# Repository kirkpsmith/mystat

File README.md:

# mystat

A USB-controlled potentiostat/galvanostat for electrochemistry measurements.

## Introduction
This repository contains all the necessary design files to build a USB-controlled potentiostat/galvanostat.  This repository is a modification of the original [tdstatv3](https://github.com/thomasdob/tdstatv3) designed by Thomas Dobbelaere and described in detail at https://arxiv.org/pdf/1701.07650.pdf.  The purpose of this fork is to make design changes that facilitate placing the instrument inside a protected enclosure suitable for an electrochemical research environment, including a wet chemical lab bench, fume hood, or glove box.

This version of the hardware design uses a PCB with dimensions of 55.5 mm by 70 mm to fit an EMI-shielded [extruded aluminum case](https://www.hammfg.com/files/parts/pdf/1457C801E.pdf) (IP 54 rated).  This board will also fit a similar watertight [extruded aluminum case](https://www.hammfg.com/files/parts/pdf/1457C801.pdf) (IP 65 rated).  The terminal block and surface mounted USB mini-B connector in the original tdstav3 design by Thomas Dobbelaere were replaced with IP 67 rated circular connectors for the USB and electrode cables.

In order to fit the case, tall components (such as the reed relays and crystal) had to be moved from the board edges that slide into the slots in the extruded aluminum.  As a result, the entire PCB layout was changed.  All traces were made as wide as possible given the PCB size constraints and component footprints.  In addition, this forked design eliminates the power and mode LEDs present in the original tdstatv3.  The choice to eliminate LEDs was made to avoid the need for creating holes in the case that would accommodate them.

## USB access on Linux
In order to access the device without requiring root privileges, create a file
`/etc/udev/rules.d/99-tdstatv3.rules` containing the line

```
SUBSYSTEM=="usb", ATTRS{idVendor}=="a0a0", ATTRS{idProduct}=="0002", GROUP="plugdev", MODE="0666"
```

If you are using an Arduino or similar to control pumps for flow battery experiments, you will need to make a similar file for that device, for example
`/etc/udev/rules.d/99-arduino.rules` and
```
SUBSYSTEM=="usb", ATTR{idVendor}=="1a86", ATTR{idProduct}=="7523", GROUP="plugdev", MODE="0666"
```

This assumes that the current user is a member of the `plugdev` group, and that the default USB Vendor and Product ID's
as coded in the microcontroller firmware are used; if not, these values need to be adjusted.

Reload of rules may be needed:
```
sudo udevadm control --reload
sudo udevadm trigger
```

## Windows Driver

To install the USB drivers in Windows, you must have Windows version 7 or later.  Download and run the program Zadig.exe found [here](https://github.com/pbatard/libwdi/releases/download/v1.5.1/zadig-2.9.exe).  The potentiostat should appear in the device list as "USB potentiostat/galvanostat".  Install the driver named "libusbK".

More information on Zadig can be found from its authors at: https://zadig.akeo.ie/

Zadig is based on libwdi and is licensed under GPLv3. The Zadig source code is found in the examples directory of the libwdi archive. The latest version of the source code may be downloaded from the git repository: https://github.com/pbatard/libwdi

## Credits
tdstatv3 created by:

* Thomas Dobbelaere
* email: thomas.dobbelaere@gmail.com

Previous fork created by:

* Matthew Yates
* email: myates@che.rochester.edu

Current fork created by:

* [Daniel Fernandez Pinto](https://chemisting.com) and [Kirk Smith](https://dualpower.supply)

## License
The contents of this repository are licensed under the GNU General Public License (GPL).

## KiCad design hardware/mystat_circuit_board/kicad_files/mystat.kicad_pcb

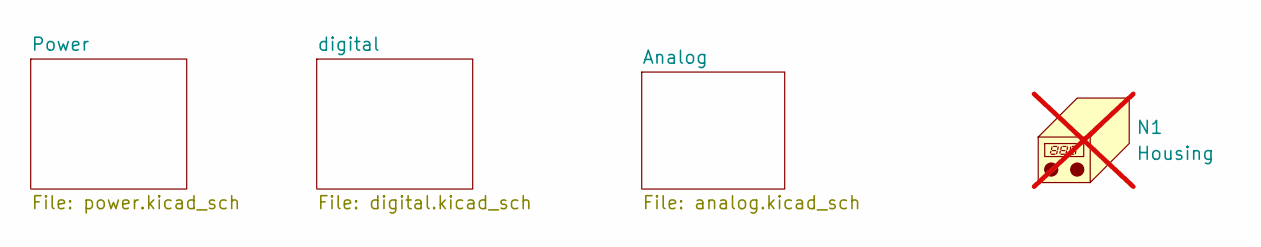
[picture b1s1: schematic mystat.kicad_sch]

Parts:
N1: Housing; MPN 1455B802; not fitted

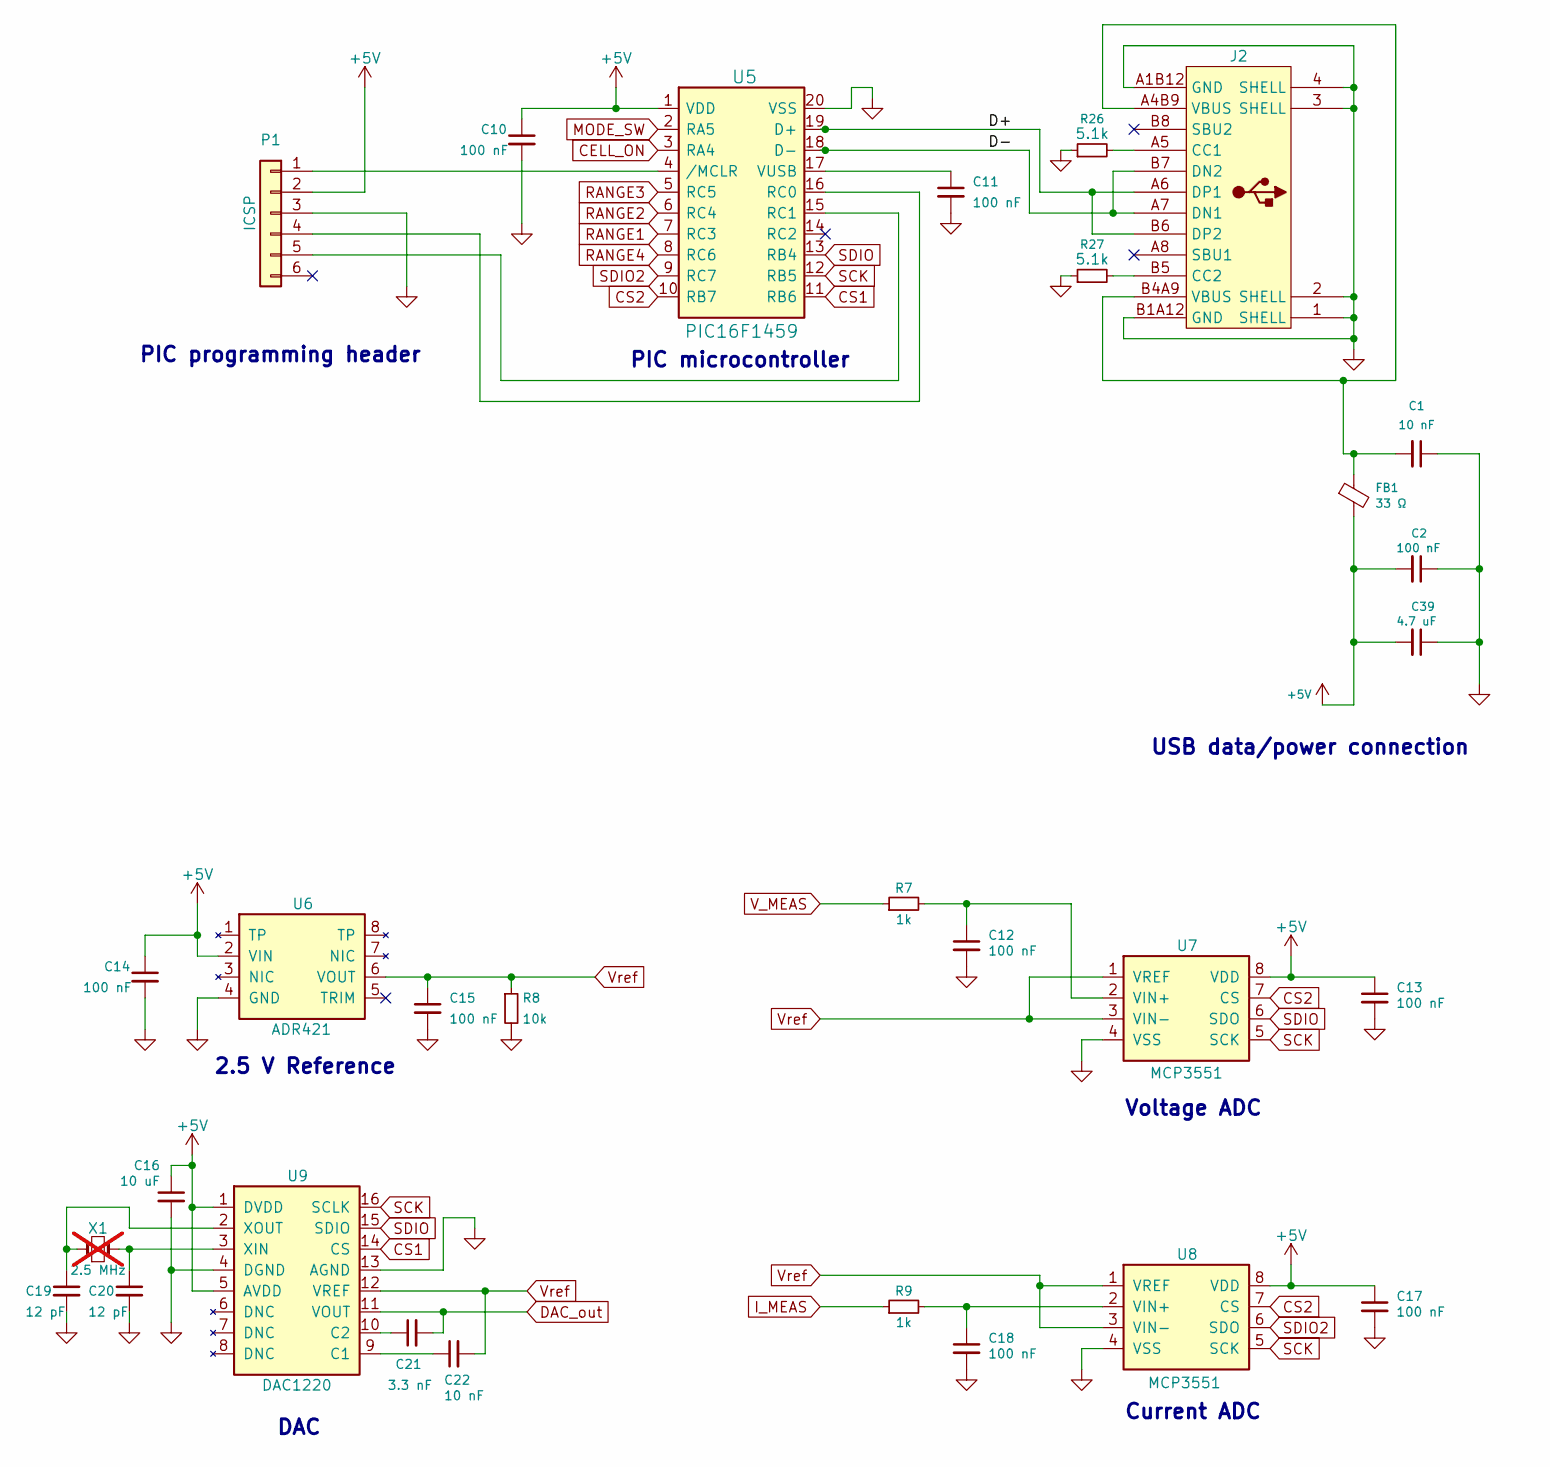
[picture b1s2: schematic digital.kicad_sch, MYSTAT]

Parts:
C1, C22: 10 nF; C_0805_2012Metric; MPN C0805C103J5GACTU
C2, C10, C11, C12, C13, C14, C15, C17, C18: 100 nF; C_0805_2012Metric; MPN 08055C104KAT2A
C16: 10 uF; C_1210_3225Metric; MPN CL32B106KBJNNWE
C19, C20: 12 pF; C_0805_2012Metric; MPN CC0805JRNPO9BN120
C21: 3.3 nF; C_0805_2012Metric; MPN GRM2165C1H332JA01D
C39: 4.7 uF; C_0805_2012Metric; MPN C2012X7R1V475K125AC
FB1: 33 Ω; C_0805_2012Metric; MPN APBH2012-330WTD16; LCSC Part C50326194
J2: USB_C_Receptacle_G-Switch_GT-USB-7010ASV; MPN GT-USB-7010ASV; LCSC Part C2988369
P1: ICSP; PinHeader_1x06_P2.54mm_Vertical; MPN HX PZ2.54-1x6P ZZ; LCSC Part C32713272
R7, R9: 1k; R_0805_2012Metric; MPN RC0805FR-071KL
R8: 10k; R_0805_2012Metric; MPN RC0805FR-0710KL
R26, R27: 5.1k; R_0805_2012Metric; LCSC Part C27834
U5: PIC16F1459; SOIC-20W; MPN PIC16F1459-I/SO
U6: ADR421; SOIC-8; MPN ADR421ARZ
U7, U8: MCP3551; SOIC-8; MPN MCP3551-E/SN; LCSC Part C1520170
U9: DAC1220; MPN DAC1220E
X1: 2.5 MHz; Crystal_HC49-U_Vertical; MPN ECS-25-S-1X; not fitted

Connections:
+5V: C2.2, C10.1, C13.1, C14.1, C16.1, C17.1, C39.2, FB1.2, P1.2, U5.1 (VDD), U6.2 (VIN), U7.8 (VDD), U8.8 (VDD), U9.1 (DVDD), U9.5 (AVDD)
/digital/D+: J2.A6 (DP1), J2.B6 (DP2), U5.19 (D+)
/digital/D-: J2.A7 (DN1), J2.B7 (DN2), U5.18 (D-)
CELL_ON: U5.3 (RA4); also elsewhere on the board
CS1: U5.11 (RB6), U9.14 (CS)
CS2: U5.10 (RB7), U7.7 (CS), U8.7 (CS)
DAC_out: C21.2, U9.11 (VOUT); also elsewhere on the board
GND: C1.1, C2.1, C10.2, C11.2, C12.2, C13.2, C14.2, C15.2, C16.2, C17.2, C18.2, C19.2, C20.2, C39.1, J2.1 (SHELL), J2.2 (SHELL), J2.3 (SHELL), J2.4 (SHELL), J2.A1B12 (GND), J2.B1A12 (GND), P1.3, R8.2, R26.1, R27.1, U5.20 (VSS), U6.4 (GND), U7.4 (VSS), U8.4 (VSS), U9.4 (DGND), U9.13 (AGND); also elsewhere on the board
I_MEAS: R9.1; also elsewhere on the board
MODE_SW: U5.2 (RA5); also elsewhere on the board
unnamed: C1.2, FB1.1, J2.A4B9 (VBUS), J2.B4A9 (VBUS)
unnamed: J2.A5 (CC1), R26.2
unnamed: J2.B5 (CC2), R27.2
unnamed: P1.1, U5.4 (/MCLR)
unnamed: P1.4, U5.16 (RC0)
unnamed: P1.5, U5.15 (RC1)
unnamed: C11.1, U5.17 (VUSB)
unnamed: C12.1, R7.2, U7.2 (VIN+)
unnamed: C18.1, R9.2, U8.2 (VIN+)
unnamed: C22.1, U9.9 (C1)
unnamed: C21.1, U9.10 (C2)
unnamed: C20.1, U9.3 (XIN), X1.2
unnamed: C19.1, U9.2 (XOUT), X1.1
RANGE1: U5.7 (RC3); also elsewhere on the board
RANGE2: U5.6 (RC4); also elsewhere on the board
RANGE3: U5.5 (RC5); also elsewhere on the board
RANGE4: U5.8 (RC6); also elsewhere on the board
SCK: U5.12 (RB5), U7.5 (SCK), U8.5 (SCK), U9.16 (SCLK)
SDIO: U5.13 (RB4), U7.6 (SDO), U9.15 (SDIO)
SDIO2: U5.9 (RC7), U8.6 (SDO)
V_MEAS: R7.1; also elsewhere on the board
Vref: C15.1, C22.2, R8.1, U6.6 (VOUT), U7.1 (VREF), U7.3 (VIN-), U8.1 (VREF), U8.3 (VIN-), U9.12 (VREF); also elsewhere on the board

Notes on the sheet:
Voltage ADC
Current ADC
PIC microcontroller
2.5 V Reference
USB data/power connection
PIC programming header
DAC

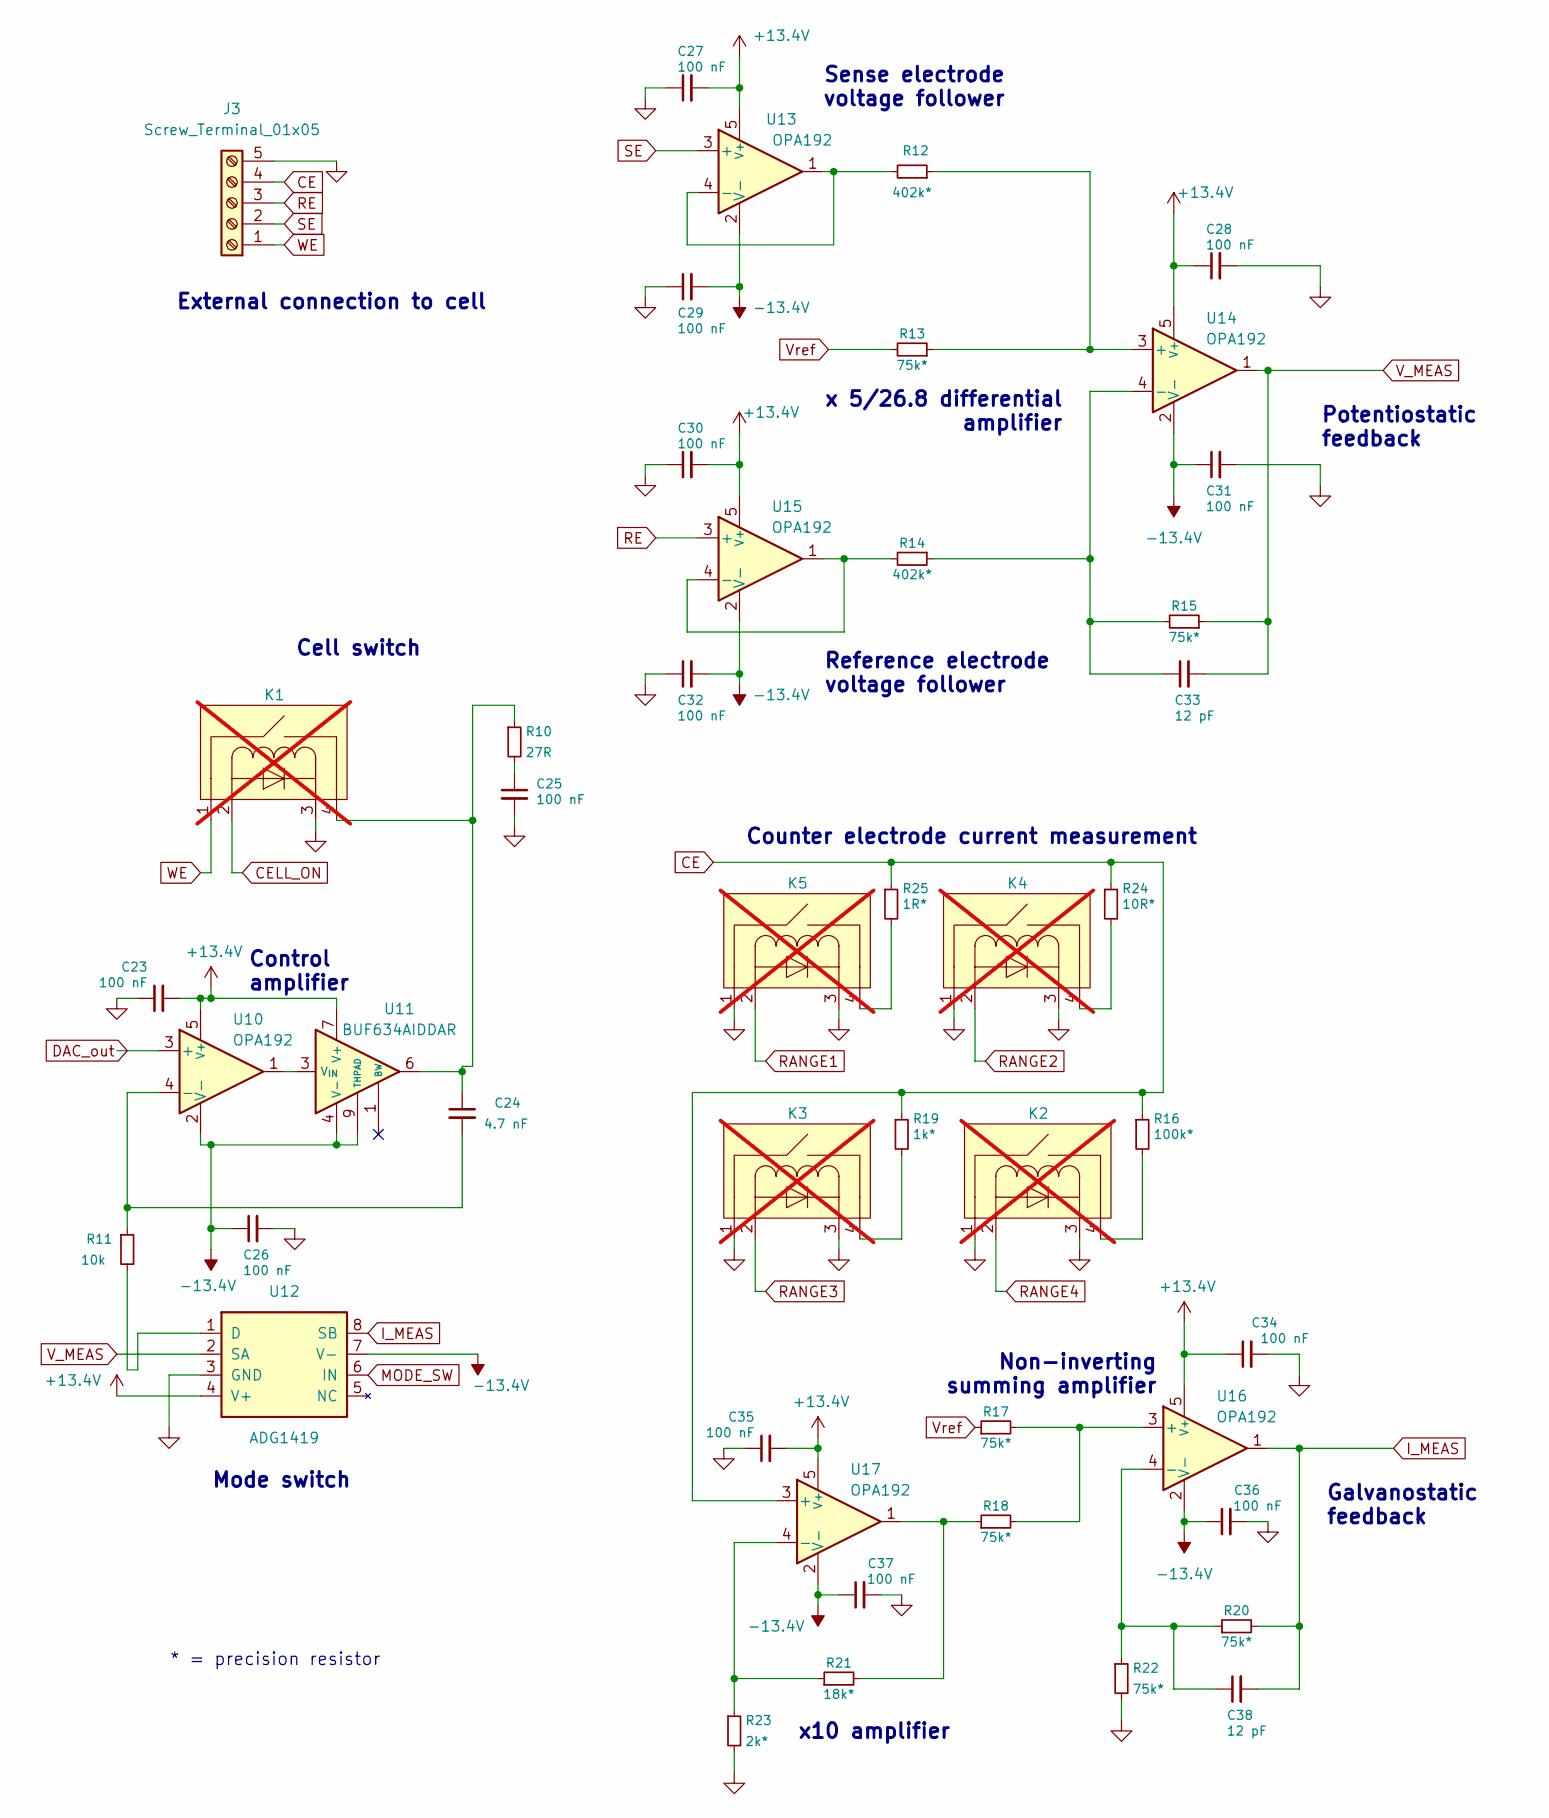
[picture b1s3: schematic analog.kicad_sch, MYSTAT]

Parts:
C23, C25, C26, C27, C28, C29, C30, C31, C32, C34, C35, C36, C37: 100 nF; C_0805_2012Metric; MPN CC0805KRX7R9BB104; LCSC Part C49678
C24: 4.7 nF; C_0805_2012Metric; MPN CC0805KRX7R9BB472; LCSC Part C107153
C33, C38: 12 pF; C_0603_1608Metric; MPN CL10C120JB8NNNC; LCSC Part C38523
J3: Screw_Terminal_01x05; CONN-TH_5P-P2.54_MX128-2.54-05P-GN01-CU-Y-A; MPN MX128-2.54-05P-GN01-Cu-Y-A; LCSC Part C5188445
K1, K2, K3, K4, K5: SIP-4_L19.6-W5.4-P5.08_9007-SPST-NO; MPN 9007-05-01; LCSC Part C6111158; not fitted
R10: 27R; R_0805_2012Metric; MPN 0805W8F270JT5E; LCSC Part C17594
R11: 10k; R_0805_2012Metric; MPN RC0805FR-0710KL; LCSC Part C84376
R12, R14: 402k*; R_0805_2012Metric; MPN TC0525B4023T5E; LCSC Part C425384
R13, R15, R17, R18, R20, R22: 75k*; R_0805_2012Metric; MPN ERA-6AEB753V; LCSC Part C473313
R16: 100k*; R_0805_2012Metric; MPN ERA-6AEB104V; LCSC Part C192074
R19: 1k*; R_0805_2012Metric; MPN ERA-6AEB102V; LCSC Part C192073
R21: 18k*; R_0805_2012Metric; MPN ERA-6AEB183V; LCSC Part C473303
R23: 2k*; R_0805_2012Metric; MPN ERA-6AEB202V; LCSC Part C417117
R24: 10R*; R_1206_3216Metric; MPN RT1206BRD0710RL; LCSC Part C309661
R25: 1R*; R_1206_3216Metric; MPN RT1206BRD071RL; LCSC Part C513714
U10, U13, U14, U15, U16, U17: OPA192; MPN OPA192IDBVR; LCSC Part C139648
U11: BUF634AIDDAR; TI_SO-PowerPAD-8_ThermalVias; MPN BUF634AIDDAR; LCSC Part C2864582
U12: ADG1419; MSOP-8_3x3mm_P0.65mm; MPN ADG1419BRMZ; LCSC Part C459694

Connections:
+13.4V: C23.2, C27.2, C28.1, C30.2, C34.1, C35.2, U10.5 (V+), U11.7 (V+), U12.4 (V+), U13.5 (V+), U14.5 (V+), U15.5 (V+), U16.5 (V+), U17.5 (V+); also elsewhere on the board
-13.4V: C26.1, C29.2, C31.1, C32.2, C36.1, C37.1, U10.2 (V-), U11.4 (V-), U11.9 (THPAD), U12.7 (V-), U13.2 (V-), U14.2 (V-), U15.2 (V-), U16.2 (V-), U17.2 (V-); also elsewhere on the board
CE: J3.4, R16.1, R19.1, R24.1, R25.1, U17.3 (+)
CELL_ON: K1.2; also elsewhere on the board
DAC_out: U10.3 (+); also elsewhere on the board
GND: C23.1, C25.2, C26.2, C27.1, C28.2, C29.1, C30.1, C31.2, C32.1, C34.2, C35.1, C36.2, C37.2, J3.5, K1.3, K2.1, K2.3, K3.1, K3.3, K4.1, K4.3, K5.1, K5.3, R22.2, R23.2, U12.3 (GND); also elsewhere on the board
I_MEAS: C38.2, R20.2, U12.8 (SB), U16.1; also elsewhere on the board
MODE_SW: U12.6 (IN); also elsewhere on the board
unnamed: C24.1, K1.4, R10.1, U11.6
unnamed: C25.1, R10.2
unnamed: K2.4, R16.2
unnamed: K3.4, R19.2
unnamed: K4.4, R24.2
unnamed: K5.4, R25.2
unnamed: C24.2, R11.1, U10.4 (-)
unnamed: U10.1, U11.3 (V_{IN})
unnamed: R11.2, U12.1 (D)
unnamed: R12.2, U13.1, U13.4 (-)
unnamed: R12.1, R13.1, U14.3 (+)
unnamed: C33.1, R14.1, R15.2, U14.4 (-)
unnamed: R14.2, U15.1, U15.4 (-)
unnamed: R17.2, R18.2, U16.3 (+)
unnamed: C38.1, R20.1, R22.1, U16.4 (-)
unnamed: R21.1, R23.1, U17.4 (-)
unnamed: R18.1, R21.2, U17.1
RANGE1: K5.2; also elsewhere on the board
RANGE2: K4.2; also elsewhere on the board
RANGE3: K3.2; also elsewhere on the board
RANGE4: K2.2; also elsewhere on the board
RE: J3.3, U15.3 (+)
SE: J3.2, U13.3 (+)
V_MEAS: C33.2, R15.1, U12.2 (SA), U14.1; also elsewhere on the board
Vref: R13.2, R17.1; also elsewhere on the board
WE: J3.1, K1.1

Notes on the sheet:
Cell switch
Mode switch
Control amplifier
x 5/26.8 differential amplifier
* = precision resistor
x10 amplifier
Potentiostatic feedback
Counter electrode current measurement
External connection to cell
Sense electrode voltage follower
Non-inverting summing amplifier
Galvanostatic feedback
Reference electrode voltage follower

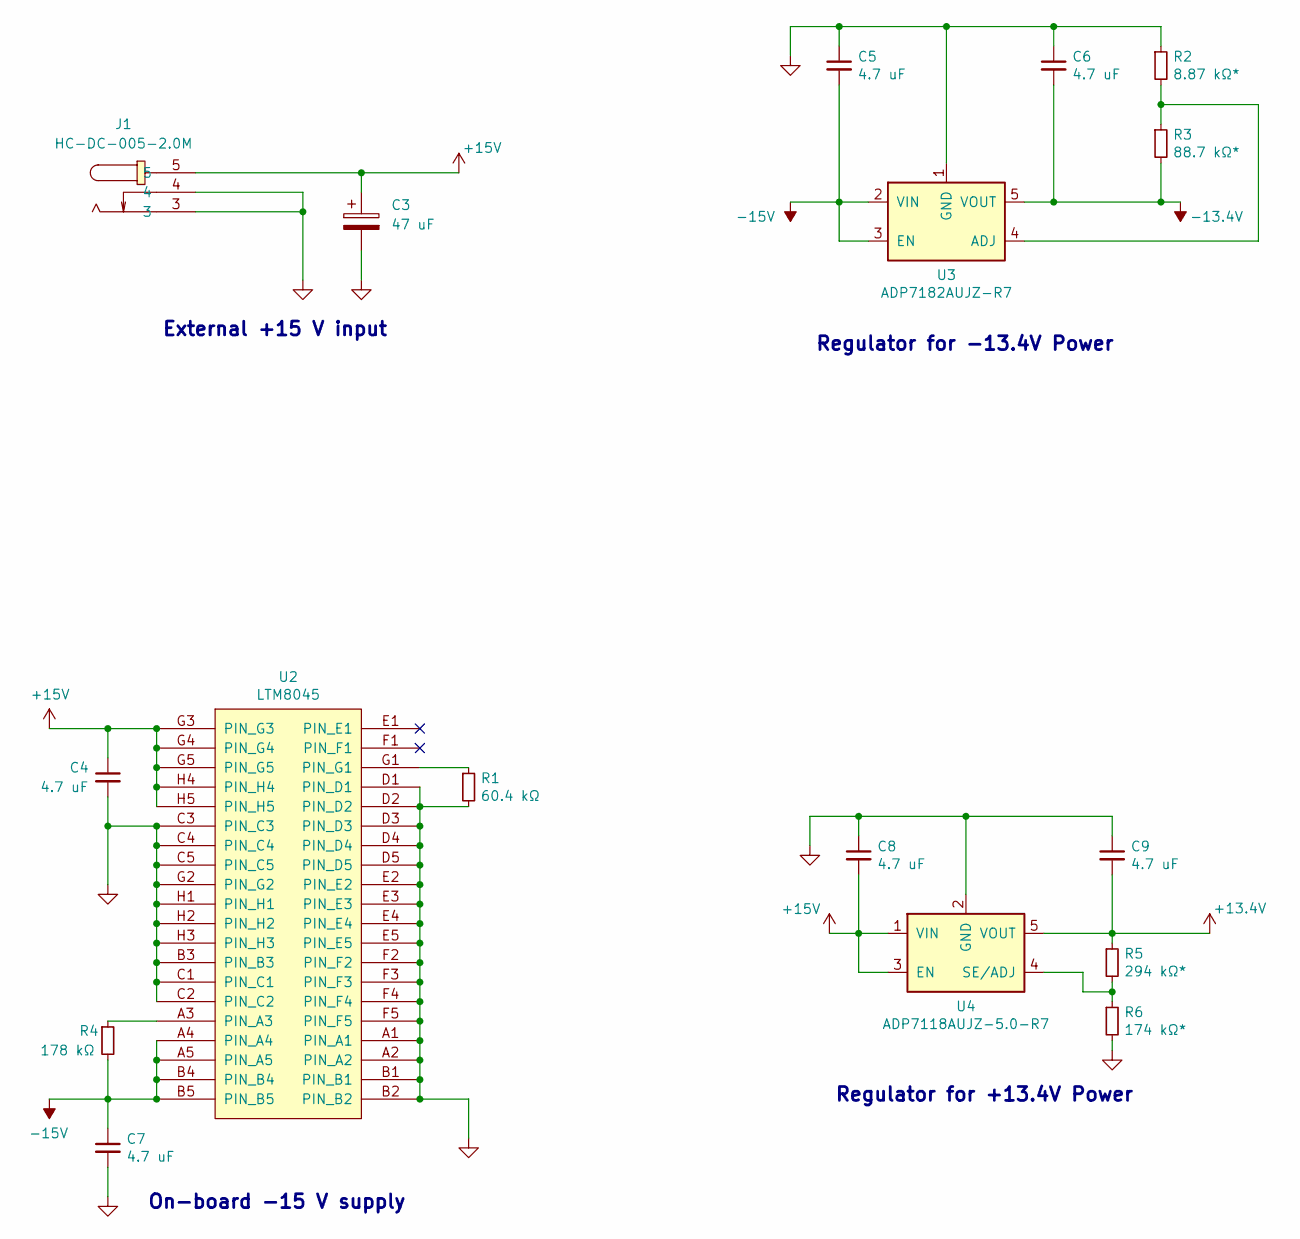
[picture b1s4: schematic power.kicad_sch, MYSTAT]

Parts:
C3: 47 uF; C_EEE-FT1V470AR; MPN EEE-FT1V470AR; LCSC Part C193627
C4, C7: 4.7 uF; C_1206_3216Metric; MPN CL31B475KBHNNNE; LCSC Part C51205
C5, C6, C8, C9: 4.7 uF; C_0805_2012Metric; MPN CL21A475KAQNNNE; LCSC Part C1779
J1: HC-DC-005-2.0M; DC-IN-TH_DC-005-2.0; MPN HC-DC-005-2.0M; LCSC Part C3010534
R1: 60.4 kΩ; R_0805_2012Metric; MPN RC0805FR-0760K4L; LCSC Part C273994
R2: 8.87 kΩ*; R_0805_2012Metric; MPN ARG05BTC8871; LCSC Part C2684603
R3: 88.7 kΩ*; R_0603_1608Metric; MPN RT0603BRD0788K7L; LCSC Part C728599
R4: 178 kΩ; R_0805_2012Metric; MPN AC0805FR-07178KL; LCSC Part C228342
R5: 294 kΩ*; R_0603_1608Metric; MPN RT0603BRD07294KL; LCSC Part C861286
R6: 174 kΩ*; R_0603_1608Metric; MPN TNPW0603174KBEEA; LCSC Part C1870358
U2: LTM8045; BGA-40_6.25x11.25mm_Layout5x8_P1.25mm; MPN LTM8045IY; LCSC Part C581193
U3: ADP7182AUJZ-R7; TSOT-23-5; MPN ADP7182AUJZ-R7; LCSC Part C514358
U4: ADP7118AUJZ-5.0-R7; TSOT-23-5; MPN ADP7118AUJZ-5.0-R7; LCSC Part C141943

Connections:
+13.4V: C9.2, R5.1, U4.5 (VOUT); also elsewhere on the board
+15V: C3.1, C4.1, C8.2, J1.5, U2.G3 (PIN_G3), U2.G4 (PIN_G4), U2.G5 (PIN_G5), U2.H4 (PIN_H4), U2.H5 (PIN_H5), U4.1 (VIN), U4.3 (EN)
-13.4V: C6.2, R3.2, U3.5 (VOUT); also elsewhere on the board
-15V: C5.2, C7.1, R4.2, U2.A4 (PIN_A4), U2.A5 (PIN_A5), U2.B4 (PIN_B4), U2.B5 (PIN_B5), U3.2 (VIN), U3.3 (EN)
GND: C3.2, C4.2, C5.1, C6.1, C7.2, C8.1, C9.1, J1.3, J1.4, R1.2, R2.1, R6.2, U2.A1 (PIN_A1), U2.A2 (PIN_A2), U2.B1 (PIN_B1), U2.B2 (PIN_B2), U2.B3 (PIN_B3), U2.C1 (PIN_C1), U2.C2 (PIN_C2), U2.C3 (PIN_C3), U2.C4 (PIN_C4), U2.C5 (PIN_C5), U2.D1 (PIN_D1), U2.D2 (PIN_D2), U2.D3 (PIN_D3), U2.D4 (PIN_D4), U2.D5 (PIN_D5), U2.E2 (PIN_E2), U2.E3 (PIN_E3), U2.E4 (PIN_E4), U2.E5 (PIN_E5), U2.F2 (PIN_F2), U2.F3 (PIN_F3), U2.F4 (PIN_F4), U2.F5 (PIN_F5), U2.G2 (PIN_G2), U2.H1 (PIN_H1), U2.H2 (PIN_H2), U2.H3 (PIN_H3), U3.1 (GND), U4.2 (GND); also elsewhere on the board
unnamed: R4.1, U2.A3 (PIN_A3)
unnamed: R1.1, U2.G1 (PIN_G1)
unnamed: R2.2, R3.1, U3.4 (ADJ)
unnamed: R5.2, R6.1, U4.4 (SE/ADJ)

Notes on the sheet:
On-board -15 V supply
Regulator for +13.4V Power
Regulator for -13.4V Power
External +15 V input

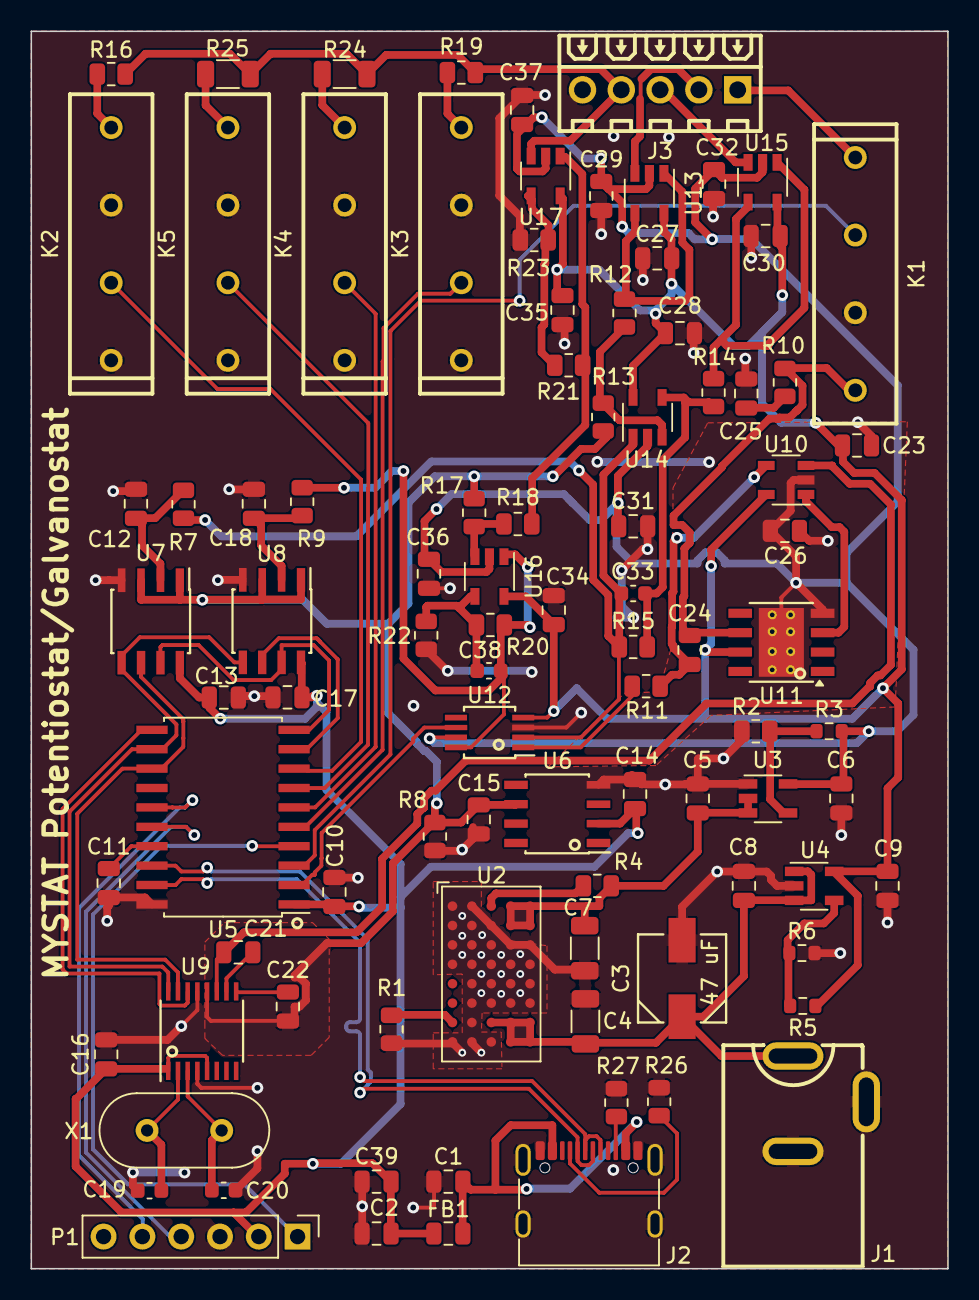
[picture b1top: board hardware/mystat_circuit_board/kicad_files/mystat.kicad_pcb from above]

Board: 4 copper layers, 60.0 x 81.0 mm, 93 parts (0 on the bottom side), 61 nets.

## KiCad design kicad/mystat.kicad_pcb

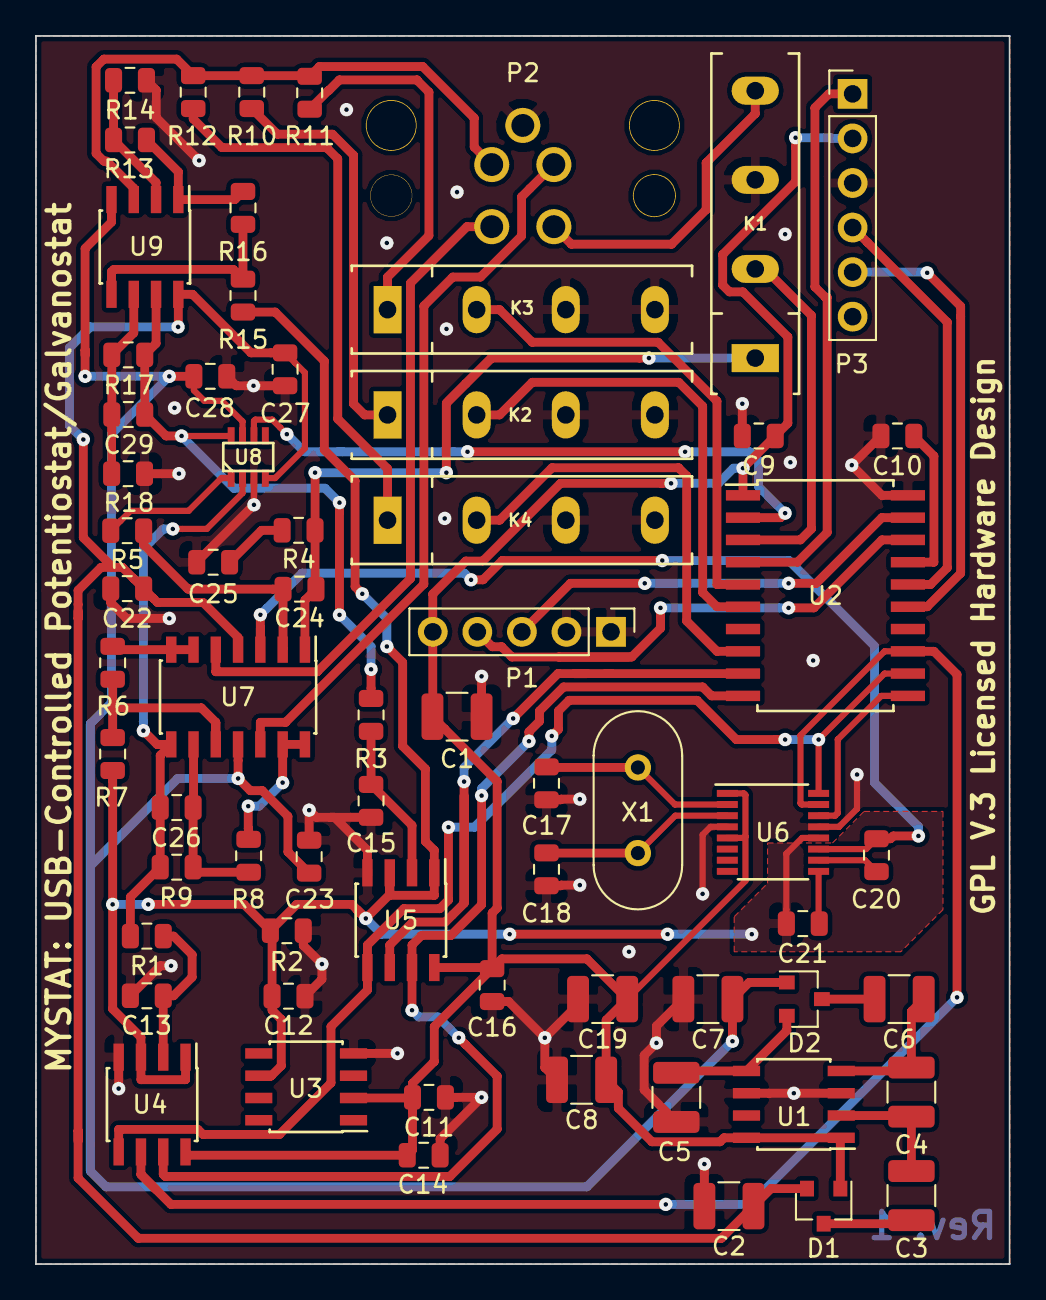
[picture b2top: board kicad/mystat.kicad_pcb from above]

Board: 2 copper layers, 55.5 x 70.0 mm, 66 parts (0 on the bottom side), 54 nets.

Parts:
C1, C2, C3, C4, C5, C6, C7, C8, C19: 10 µF; C_1210_3225Metric
C9, C10, C11, C12, C13, C14, C15, C16, C22, C23, C25, C27, C28: 0.1 µF; C_0805_2012Metric
C17, C18, C26, C29: 12 pF; C_0805_2012Metric
C20: 3.3 nF; C_0805_2012Metric
C21: 10 nF; C_0805_2012Metric
C24: 4700 pF; C_0805_2012Metric
D1, D2: BAT721S; SOT-23
K1, K2, K3, K4: 9007-05-01; RELAY-9007
P1: USB Terminal; PinHeader_1x05_P2.54mm_Vertical
P2: CELL; T4145035041-001
P3: ICSP; PinHeader_1x06_P2.54mm_Vertical
R1, R3: 1k; R_0805_2012Metric
R2, R5: 10k; R_0805_2012Metric
R4: 27R; R_0805_2012Metric
R6, R8: 240k*; R_0805_2012Metric
R7, R9, R15, R16, R17, R18: 75k*; R_0805_2012Metric
R10: 10R*; R_0805_2012Metric
R11: 1k*; R_0805_2012Metric
R12: 100k*; R_0805_2012Metric
R13: 18k*; R_0805_2012Metric
R14: 2k*; R_0805_2012Metric
U1: LM2662; SOIC-8_3.9x4.9mm_P1.27mm
U2: PIC16F1459; SOIC-20W_7.5x12.8mm_P1.27mm
U3: ADR421; SOIC-8_3.9x4.9mm_P1.27mm
U4, U5: MCP3553; SOIC-8_3.9x4.9mm_P1.27mm
U6: DAC1220; SSOP-16_3.9x4.9mm_P0.635mm
U7: OPA4192; SOIC-14_3.9x8.7mm_P1.27mm
U8: DG449; sot23-8
U9: OPA2192; SOIC-8_3.9x4.9mm_P1.27mm
X1: 2.5 MHz; Crystal_HC49-U_Vertical

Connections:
+5V: C1.1, C8.1, C9.1, C11.1, C14.1, C16.1, C19.1, D1.1, P1.1, P3.2, U1.1, U1.8, U2.1, U3.2, U4.8, U5.8, U6.1, U6.5
+9V: C2.1, C22.2, C27.2, D1.2, U7.4, U8.4, U9.8
-9V: C7.2, C23.1, C28.1, D2.1, U7.11, U8.7, U9.4
/CE: P2.3, R10.1, R11.1, R12.1, U9.3
/CELL_ON: K1.2, U2.3
/CS1: U2.11, U6.14
/CS2: U2.10, U4.7, U5.7
/ICSPCLK: P3.5, U2.15
/ICSPDAT: P3.4, U2.16
/I_MEAS: C29.2, R3.1, R17.2, U8.8, U9.7
/MCLR: P3.1, U2.4
/MODE_SW: U2.2, U8.6
/RANGE1: K2.2, U2.6
/RANGE2: K3.2, U2.5
/RANGE3: K4.2, U2.8
/RE: P2.4, U7.12
/SCK: U2.12, U4.5, U5.5, U6.16
/SDIO: U2.13, U4.6, U6.15
/SDIO2: U2.9, U5.6
/SE: P2.2, U7.5
/USB_D+: P1.3, U2.19
/USB_D-: P1.2, U2.18
/VREF: C12.1, C21.2, R2.1, R7.2, R15.1, U3.6, U4.1, U4.3, U5.1, U5.3, U6.12
/V_MEAS: C26.2, R1.1, R9.1, U7.8, U8.2
/WE: K1.4, P2.1
GND: C1.2, C2.2, C5.1, C7.1, C8.2, C9.2, C10.2, C11.2, C12.2, C13.2, C14.2, C15.2, C16.2, C17.2, C18.2, C19.2, C22.1, C23.2, C25.2, C27.1, C28.2, K1.3, K2.3, K2.4, K3.3, K3.4, K4.3, K4.4, P1.4, P1.5, P2.5, P3.3, R2.2, R14.2, R18.2, U1.3, U1.6, U2.20, U3.4, U4.4, U5.4, U6.4, U6.13, U8.3
unnamed: C3.1, D1.3
unnamed: C3.2, C4.1, U1.2
unnamed: C4.2, C6.1, U1.4
unnamed: C5.2, D2.2, U1.5
unnamed: C6.2, D2.3
unnamed: C10.1, U2.17
unnamed: C13.1, R1.2, U4.2
unnamed: C15.1, R3.2, U5.2
unnamed: C17.1, U6.2, X1.1
unnamed: C18.1, U6.3, X1.2
unnamed: C20.1, U6.10
unnamed: C20.2, U6.11, U7.3
unnamed: C21.1, U6.9
unnamed: C24.1, K1.1, R4.1, U7.1
unnamed: C24.2, R5.1, U7.2
unnamed: C25.1, R4.2
unnamed: C26.1, R8.1, R9.2, U7.9
unnamed: C29.1, R17.1, R18.1, U9.6
unnamed: K2.1, R10.2
unnamed: K3.1, R11.2
unnamed: K4.1, R12.2
unnamed: R5.2, U8.1
unnamed: R6.1, U7.6, U7.7
unnamed: R6.2, R7.1, U7.10
unnamed: R8.2, U7.13, U7.14
unnamed: R13.1, R14.1, U9.2
unnamed: R13.2, R16.1, U9.1
unnamed: R15.2, R16.2, U9.5

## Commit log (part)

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2018-06-28 Update README.md
    Added text explaining changes made to original tdstatv3 design.
2018-07-02 Delete photograph.jpg
    Image does not represent modified design.
2018-07-02 Update parts_list.txt
    Removed indicator LEDs.
2018-07-02 Update parts_list.txt
    Replaced terminal block with shielded 4-position circular connector.
2018-07-02 Update parts_list.txt
    Replaced SMD usb port with 5 pin receptacle for mating with a Bulgin panel mounted USB cable.
2018-07-02 Delete pcb_3dview.png
    Does not illustrate modified design.
2018-07-02 Add files via upload
    3D rendering of modified PCB design.
2018-07-02 Add files via upload
    Shows modified board layout.
2018-07-02 Delete full_schematic.pdf
    Does not represent modified design.
2018-07-02 Add files via upload
    Modified schematic to remove indicator LEDs.
2018-07-02 Delete tdstatv3-B.Cu.gbl
    Does not represent modified design.
2018-07-02 Add files via upload
    Showing modified PCB design.
2018-07-02 Delete tdstatv3-B.Mask.gbs
    Does not represent modified PCB layout.
2018-07-02 Delete tdstatv3-F.Cu.gtl
    Does not represent modified PCB layout.
2018-07-02 Delete tdstatv3-F.Mask.gts
    Does not represent modified PCB layout.
2018-07-02 Delete tdstatv3-F.SilkS.gto
    Does not represent modified PCB layout.
2018-07-02 Delete tdstatv3-NPTH.drl
    Does not represent modified PCB layout.
2018-07-02 Delete tdstatv3.drl
    Does not represent modified PCB layout.
2018-07-02 Add files via upload
    Modified PCB layout/design.
2018-07-02 Add files via upload
    3D rendering of modified PCB layout/design.
2018-07-02 Delete duo_led_3mm_green.wings
    Not used in modified design.
2018-07-02 Delete duo_led_3mm_green.wrl
    Not used in modified design.
2018-07-02 Delete led_3mm_red.wings
    Not used in modified design.
2018-07-02 Delete led_3mm_red.wrl
    Not used in modified design.
2018-07-02 Add files via upload
    3D rendering of TE Connectivity part: 215297-5
2018-07-02 Delete TerminalBlock_Phoenix_MKDS1_5_3mm5.kicad_mod
    Not used in modified design.
2018-07-02 Add files via upload
    Based on the datasheet for TE Connectivity part: T4145035041-001
2018-07-02 Add files via upload
    Used for TE Connectivity part: 215297-5
2018-07-02 Delete fp-lib-table
    Does not represent modified PCB layout/design.
2018-07-02 Delete mylib.bck
    Does not represent modified PCB layout/design.
2018-07-02 Delete mylib.dcm
    Does not represent modified PCB layout/design.
2018-07-02 Delete tdstatv3
    Does not represent modified PCB layout/design.
2018-07-02 Delete tdstatv3-cache.lib
    Does not represent modified PCB layout/design.
2018-07-02 Delete tdstatv3.bak
    Does not represent modified PCB layout/design.
2018-07-02 Delete tdstatv3.csv
    Does not represent modified PCB layout/design.
2018-07-02 Delete tdstatv3.kicad_pcb
    Does not represent modified PCB layout/design.
2018-07-02 Delete tdstatv3.kicad_pcb-bak
    Does not represent modified PCB layout/design.
2018-07-02 Delete tdstatv3.pro
    Does not represent modified PCB layout/design.
2018-07-02 Delete tdstatv3.sch
    Does not represent modified PCB layout/design.
2018-07-02 Delete tdstatv3.xml
    Does not represent modified PCB layout/design.
2018-07-02 Add files via upload
    Kicad files for modified PCB layout/design
2018-07-02 Delete tdstatv3.py
    Changing file name,
2018-07-02 Add files via upload
    Changed file name and altered ADC reading interval to match rate of the MCP3553 chip.
2018-07-14 Update README.md
    New PCB dimensions and new case selected.
2018-07-14 Add files via upload
    Updated revision date.
2018-07-14 Add files via upload
    Changed layout. Added guard ring for the DAC1220. Used wider traces. Manually routed everything.
2018-07-14 Delete mystatv1.kicad_pcb-bak
    No need for old backup file.
2018-07-16 Add files via upload
    Added symbol for the USB terminal with Pin 1 labeled for power input.
2018-07-16 Add files via upload
    Name changed. Created updated version using Kicad version 5.
2018-07-16 Add files via upload
    Name changed. Created using latest schematic in Kicad version 5.
2018-07-16 Add files via upload
    Named changed. PCB dimensions changed to 80mm x 80mm. Used wider traces throughout. Added guard ring for U6 following Texas Instruments datasheet guidelines. Reorganized components to minimize length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
2018-07-16 Add files via upload
    Bill of materials created using KiBOM_CLI plugin in Kicad version 5. Added manufacturer and part numbers to facilitate creating a shopping cart at Digi-Key or other supplier.
2018-07-16 Add files via upload
    Used unpolarized capacitor symbols through since the ceramic capacitors are all non-polarized.
2018-07-16 Add files via upload
    Showing new PCB layout.
2018-07-17 Delete mystat-Edge.Cuts.gbr
    Changed to Protel file extensions.
2018-07-17 Delete mystatv1-Edge.Cuts.gm1
    Replaced with revised layout.
2018-07-17 Delete mystatv1-B.Mask.gbs
    Replaced with revised layout.
2018-07-17 Delete mystatv1-F.Mask.gts
    Replaced with revised layout.
2018-07-17 Delete mystatv1-F.SilkS.gto
    Replaced with revised layout.
2018-07-17 Delete mystatv1-F.Paste.gtp
    Replaced with revised layout.
2018-07-17 Delete mystatv1-B.Cu.gbl
    Replaced with revised layout.
2018-07-17 Delete mystatv1-F.Cu.gtl
    Replaced with revised layout.
2018-07-17 Delete BAT721.pdf
    Link to datasheet provided in revised schematic.
2018-07-17 Delete DAC1220.pdf
    Link to datasheet provided in revised schematic.
2018-07-17 Delete DG449.pdf
    Link to datasheet provided in revised schematic.
2018-07-17 Delete LM2662.pdf
    Link to datasheet provided in revised schematic.
2018-07-17 Delete MCP3550-50.pdf
    Link to datasheet provided in revised schematic.
2018-07-17 Delete OPA4192.pdf
    Link to datasheet provided in revised schematic.
2018-07-17 Delete spst_reed_relay_9007-05-01.pdf
    Link to datasheet provided in revised schematic.
2018-07-17 Update README.md
    Removed all PDF files and replaced with links to datasheets in the revised Kicad schematic.
2018-07-26 Add files via upload
    Picture of board with latest revision of PCB layout.
2018-07-26 Update README.md
    Edited to explain design choices made in latest PCB layout.
2018-07-26 Update README.md
    Changed title.
2018-07-26 Add files via upload
    Changed name and date.
2018-07-26 Add files via upload
    Shows latest PCB layout.
2018-07-26 Add files via upload
    Modified PCB layout.
2018-07-26 Add files via upload
    Changed title and date with modified PCB layout.
2018-07-26 Add files via upload
    Modified PCB layout. Made overall PCB dimensions smaller to fit the chosen case, all traces were made as wide as possible, changed relative position of all components in an attempt to minimize overal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
2018-07-26 Add files via upload
    Used with latest PCB layout.
2018-07-26 Add files via upload
    Removed static link to Dobbelaere home directory for 3D image of component. Added 3D image scaling to convert dimensions to English system.
2018-07-26 Add files via upload
    Fixed error in footprint. The largest mechanical holes were moved slightly close together. This should allow the plastic clips on this component to attach to the PCB.
2018-07-26 Add files via upload
    Added link to 3D image of component. Added scaling, rotation, and offset so that the 3D image matches the footprint.
2018-07-26 Delete sot23-8.wings
    Used standard SOT-23-8 image from Kicad 5 instead.
2018-07-26 Delete sot23-8.wrl
    Used standard SOT-23-8 image from Kicad 5 instead.
2018-07-26 Delete usb_B_mini_smd.wings
    Not using this component in revised design.
2018-07-26 Delete usb_B_mini_smd.wrl
    Not using this component in revised design.
2018-07-26 Delete crystal_hc-49u.wrl
    Used standard Crystal_HC49-U_Vertical image from Kicad 5 instead.
2018-07-26 Add files via upload
    Revised PCB layout.
2018-07-26 Delete mystat-PTH.drl
    Combined PTH and NPTH into one drl file with revised layout.
2018-07-26 Delete mystat-NPTH.drl
    Combined PTH and NPTH into one drl file with revised PCB layout.
2018-07-26 Update README.md
    Corrected PCB width dimension.
2018-07-27 Add files via upload
    Changed title and date.
2018-07-27 Delete mystat-B.SilkS.gbo
    Not using silk screen on back side of board.
2018-07-27 Delete mystat-B.Paste.gbp
    No SMD parts on back side of board.
2018-07-27 Add files via upload
    New layout of traces for better ground return paths.
2018-07-27 Delete mystatv1.py
    Changing file name, but using original code from tdstatv3.
2018-07-27 Add files via upload
    Same Python code as in tdstatv3, just a different file name to match the naming of this fork.
2018-07-27 Delete mystat_bom_1.csv
    New BOM will be uploaded to main project page.
2018-07-27 Add files via upload
    3D image of circular connector created from manufacturer supplied *.stp file.
2018-07-27 Add files via upload
    Minor layout changes to facilitate trace routing.
2018-07-27 Update README.md
    Fixed typo.
2018-07-27 Update README.md
    Removed mention of a photograph, since I don't have one.
2018-07-27 Add files via upload
    Added link to 3D image.
2018-07-27 Add files via upload
    Footprint updated for circular connector.
2018-07-27 Update README.md
    Added description of bill of materials csv file.
2018-07-27 Delete parts_list.txt
    Replaced with parts list from Digikey shopping cart.
2018-07-27 Add files via upload
    Parts list from Digiket shopping cart.
2018-07-27 Update README.md
    Added description of parts list.
2018-07-27 Add files via upload
    Updated part numbers with what is presently in stock at Digikey.
2018-07-27 Add files via upload
    Updated with parts presently in stock at Digikey.
2023-11-01 add HVC to charge-based cutoff, change to QtWidgets
    Daniel added the HVC functionality, I had to replace many calls with QtWidgets to get the code to run, not sure why
2023-11-01 Update mystat.py, add QtWidgets for QFileDialog
2024-04-07 Daniel added functionality to connect to Arduino for pump speed control
2024-04-27 Daniel fixed serial connections to motor control arduino, refresh serial ports and simultaneous motor speed control
2024-05-20 added files for printable case that Josh Hauser designed
2024-07-03 arduino pump control now only updates pump speed when slider is released, not continuously as slider moves to new values
2025-03-20 made requirements.txt and install instructions
2025-03-20 removed mystat.spec file from pyinstaller
2025-03-29 added troubleshooting to docs, first compiled linux app
2025-04-02 change to gitignore to avoid large compiled binary
2025-04-17 Daniel added pump speed measurements for brushless stepper motor KPK200 pumps
2025-04-17 Daniel added pump speed measurements for kpk200
2025-05-31 renamed pump controls
2025-09-01 moved things around to match as closely as possible the Zenodo upload from Yates
2025-12-12 changed deprecated scipy function name in control app
2025-12-13 updated function calls away from deprecated versions, update requirements.txt (somehow irrelevant packages were present)
2026-03-20 added variable to store file handle, so that a new one is not created with each measurement
2026-03-23 made arduino connection like mystat based on PID/VID, add ubound validation from 0-3 V, add feature to edit parameters while cycling, tidy up pump GUI so RPM is readable even when not cycling and the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
2026-03-27 update to KiCAD 10
2026-05-01 script to build appimage based on pyinstaller
2026-05-01 appimage script
2026-05-01 removed auto-download of appimagetool in build script
2026-05-01 revert to KiCAD 10 state before attempting reed relay changes, to merge into master
2026-05-01 fix requirments.txt
2026-05-01 fix requirements
2026-05-01 removed serial and glob from python imports. fixed build script to avoid Qt5 plugins, app is now half the size!
2026-05-01 update readmes

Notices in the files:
kicad/mystat.kicad_pcb:
GPL v.3 Open Source Hardware Design
GPL V.3 Licensed Hardware Design
parts and their libraries:
Copyright 2016 Accelerated Designs. All rights reserved.
